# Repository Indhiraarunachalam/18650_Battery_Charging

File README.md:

# 18650 Battery Charging PCB Design

## Overview

This project presents the PCB design of a 18650 Lithium-Ion Battery Charging Circuit developed using **KiCad**. The design includes a TP4056 battery charging IC, battery protection circuit, charging status indicators, USB Micro power input, and battery output connector.

The project covers the complete PCB design workflow from schematic design to PCB layout, design verification, and Gerber generation.

---

## Features

- TP4056 Lithium-Ion Battery Charging IC
- USB Micro Power Input
- Battery Protection Circuit
- Charging Status LEDs
- Battery Output Connector
- ON/OFF Slide Switch
- Two-Layer PCB Design

---

## Software Used

- KiCad

---

## Hardware Components

- TP4056 Battery Charging IC
- FS312F Battery Protection IC
- FS8205 Dual MOSFET
- USB Micro Connector
- LEDs
- Slide Switch
- Resistors
- Capacitors
- Pin Headers

---

## Design Flow

1. Schematic Design
2. ERC Verification
3. PCB Layout
4. Component Placement
5. PCB Routing
6. DRC Verification
7. Gerber Generation

---

## Design Verification

- ERC Passed ✅
- DRC Passed ✅
- Gerber Files Generated Successfully ✅
- Ready for PCB Fabrication ✅

---

## Repository Structure

```
18650_Battery_Charging_PCB_Design
│
├── 18650_Battery_Charging.kicad_sch
├── 18650_Battery_Charging.kicad_pcb
├── README.md
│
├── Gerber/
│
└── Images/
    ├── 18650_Battery_Schematic.png
    ├── 18650_Battery_TopLayer.png
    ├── 18650_Battery_BottomLayer.png
    └── 18650_Battery_3D_View.png
```

---

## Project Images

### Schematic

---

### PCB Layout - Top Layer

---

### PCB Layout - Bottom Layer

---

### 3D View

---

## Learning Outcomes

- Designed a Lithium-Ion battery charging PCB using KiCad.
- Learned schematic capture and PCB layout design.
- Practiced component placement and PCB routing.
- Performed ERC and DRC verification.
- Generated Gerber files for PCB fabrication.

---

## Author

**Indhira A**

Electronics and Communication Engineering Student

Interested in PCB Design, Embedded Systems, and IoT.

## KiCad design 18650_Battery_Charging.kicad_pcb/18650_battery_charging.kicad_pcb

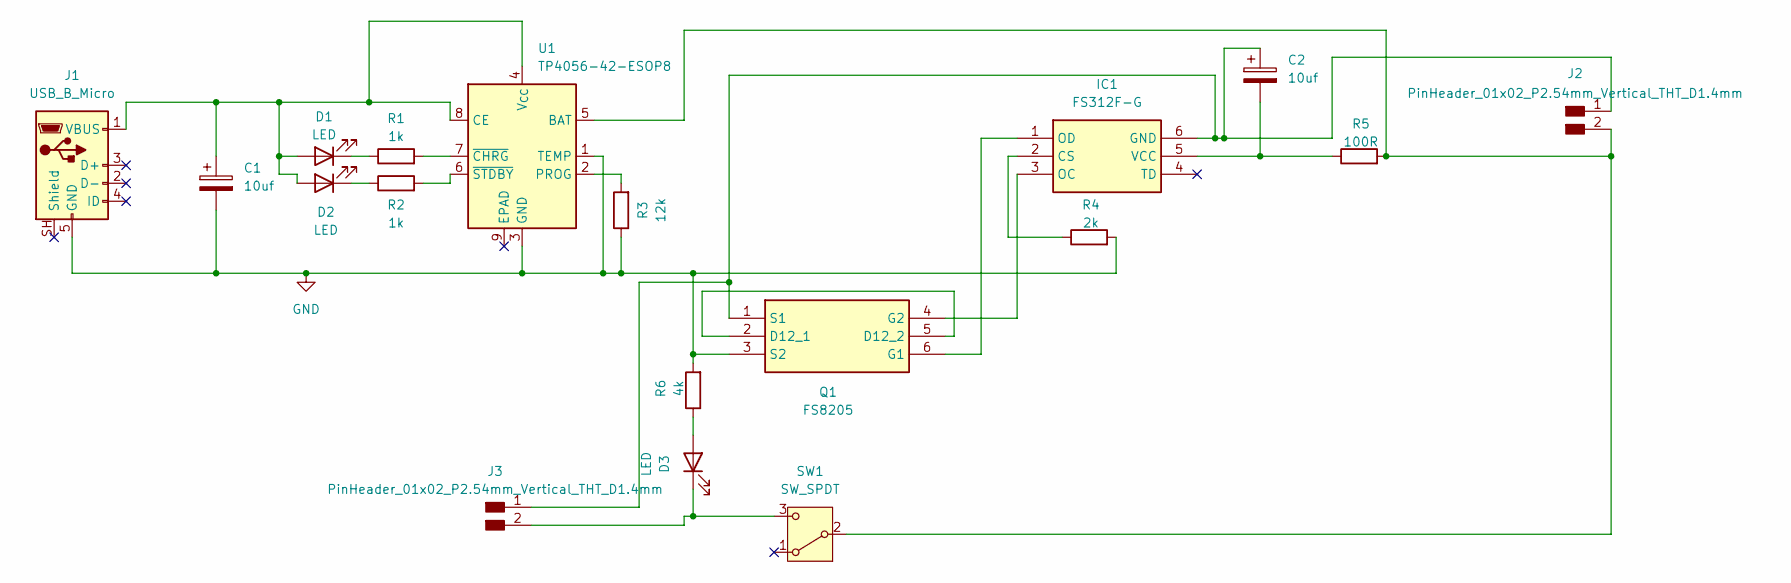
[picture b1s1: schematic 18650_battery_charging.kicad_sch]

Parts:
C1, C2: 10uf; CP_Radial_D5.0mm_P2.00mm
D1, D2, D3: LED; LED_D5.0mm
IC1: FS312F-G; SOT95P280X145-6N; Manufacturer_Part_Number FS312F-G
J1: USB_B_Micro; USB_Micro-B_Molex-105017-0001
J2, J3: PinHeader_01x02_P2.54mm_Vertical_THT_D1.4mm
Q1: FS8205; Manufacturer_Part_Number FS8205
R1, R2: 1k; R_Axial_DIN0207_L6.3mm_D2.5mm_P7.62mm_Horizontal
R3: 12k; R_Axial_DIN0207_L6.3mm_D2.5mm_P7.62mm_Horizontal
R4: 2k; R_Axial_DIN0207_L6.3mm_D2.5mm_P7.62mm_Horizontal
R5: 100R; R_Axial_DIN0207_L6.3mm_D2.5mm_P7.62mm_Horizontal
R6: 4k; R_Axial_DIN0207_L6.3mm_D2.5mm_P7.62mm_Horizontal
SW1: SW_SPDT; SW_Slide_SPDT_Straight_CK_OS102011MS2Q
U1: TP4056-42-ESOP8; SOIC-8-1EP_3.9x4.9mm_P1.27mm_EP2.41x3.3mm_ThermalVias

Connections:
GND: C1.2, J1.5 (GND), Q1.3 (S2), R3.1, R4.2, R6.2, U1.1 (TEMP), U1.3 (GND)
unnamed: C1.1, D1.2 (A), D2.2 (A), J1.1 (VBUS), U1.4 (V_{CC}), U1.8 (CE)
unnamed: D1.1 (K), R1.1
unnamed: D2.1 (K), R2.1
unnamed: D3.2 (A), R6.1
unnamed: D3.1 (K), J3.2, SW1.3 (C)
unnamed: IC1.2 (CS), R4.1
unnamed: C2.1, IC1.6 (GND), J2.1, J3.1, Q1.1 (S1)
unnamed: IC1.3 (OC), Q1.4 (G2)
unnamed: IC1.1 (OD), Q1.6 (G1)
unnamed: C2.2, IC1.5 (VCC), R5.1
unnamed: J2.2, R5.2, SW1.2 (B), U1.5 (BAT)
unnamed: Q1.2 (D12_1), Q1.5 (D12_2)
unnamed: R3.2, U1.2 (PROG)
unnamed: R1.2, U1.7 (~CHRG)
unnamed: R2.2, U1.6 (~STDBY)

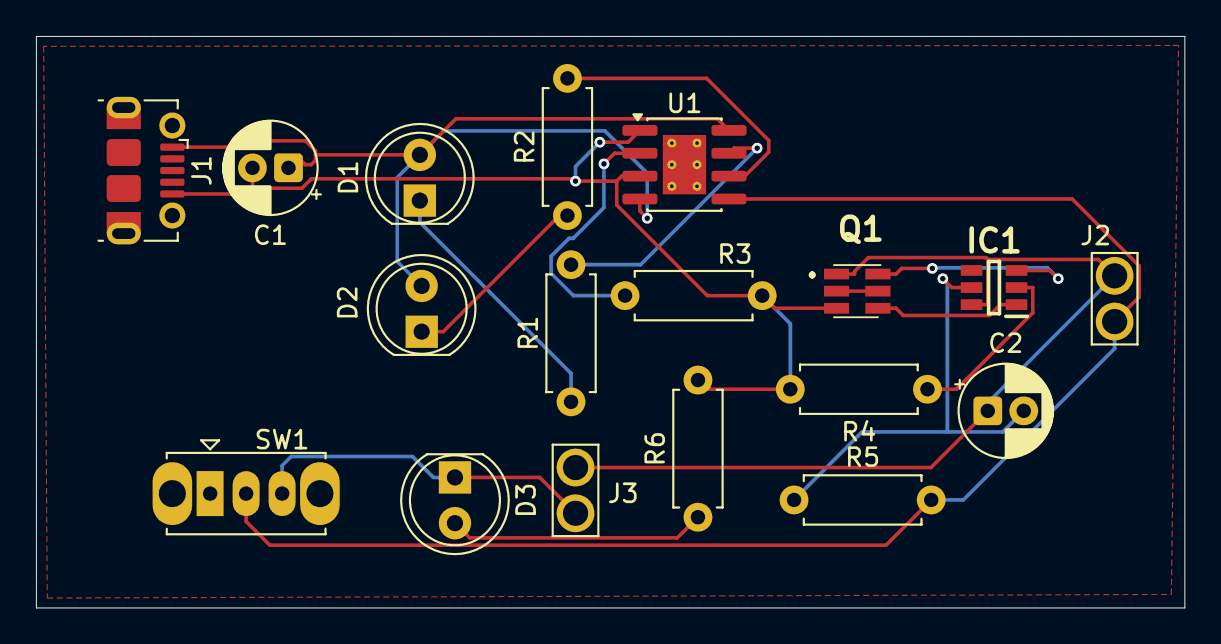
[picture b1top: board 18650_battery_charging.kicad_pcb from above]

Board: 2 copper layers, 63.8 x 31.8 mm, 18 parts (0 on the bottom side), 16 nets.
